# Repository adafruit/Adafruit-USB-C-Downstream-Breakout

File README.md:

## Adafruit USB C Breakout Board - Downstream Connection PCB

<a href="http://www.adafruit.com/products/4090"><br/>
Click here to purchase one from the Adafruit shop</a>

PCB files for the Adafruit USB C Breakout Board - Downstream Connection. Format is EagleCAD schematic and board layout
* https://www.adafruit.com/product/4090

### Description

Throw out all those Mini and Micro B USB cables you have in a plastic bin - the next generation of USB connectors is here with **USB C!** You will start to see these connectors pop up on all sorts of devices, as the industry moves from micro B or lightening to the new standard. Well, at least until the next standard comes out

USB C features a symmetric/reversible connector, more data pins and higher current output capability. But, for most developers, the pin usage you know and love from older USB will work just fine. This breakout gives you all the basics you need and a resistor configuration that mimics classic USB 2.0 for a downstream connection

The two 5.1K resistors on the **CC1** pins indicate to the upstream port to provide 5V and up to 1.5A (whether the upstream can supply that much current depends on what you're connecting to.

For most usages, you can just connect **VBUS** to your 5V input, **GND** to ground, and **D+** and **D-** as you expect. You can monitor the CC and SBU pins to determine cable polarity, or send side-band data. Or leave them disconnected

[For more details, we like this introduction to USB C app note](http://ww1.microchip.com/downloads/en/appnotes/00001953a.pdf)
### License

Adafruit invests time and resources providing this open source design, please support Adafruit and open-source hardware by purchasing products from [Adafruit](https://www.adafruit.com)!

Designed by Limor Fried/Ladyada for Adafruit Industries.

Creative Commons Attribution/Share-Alike, all text above must be included in any redistribution. See license.txt for additional details.

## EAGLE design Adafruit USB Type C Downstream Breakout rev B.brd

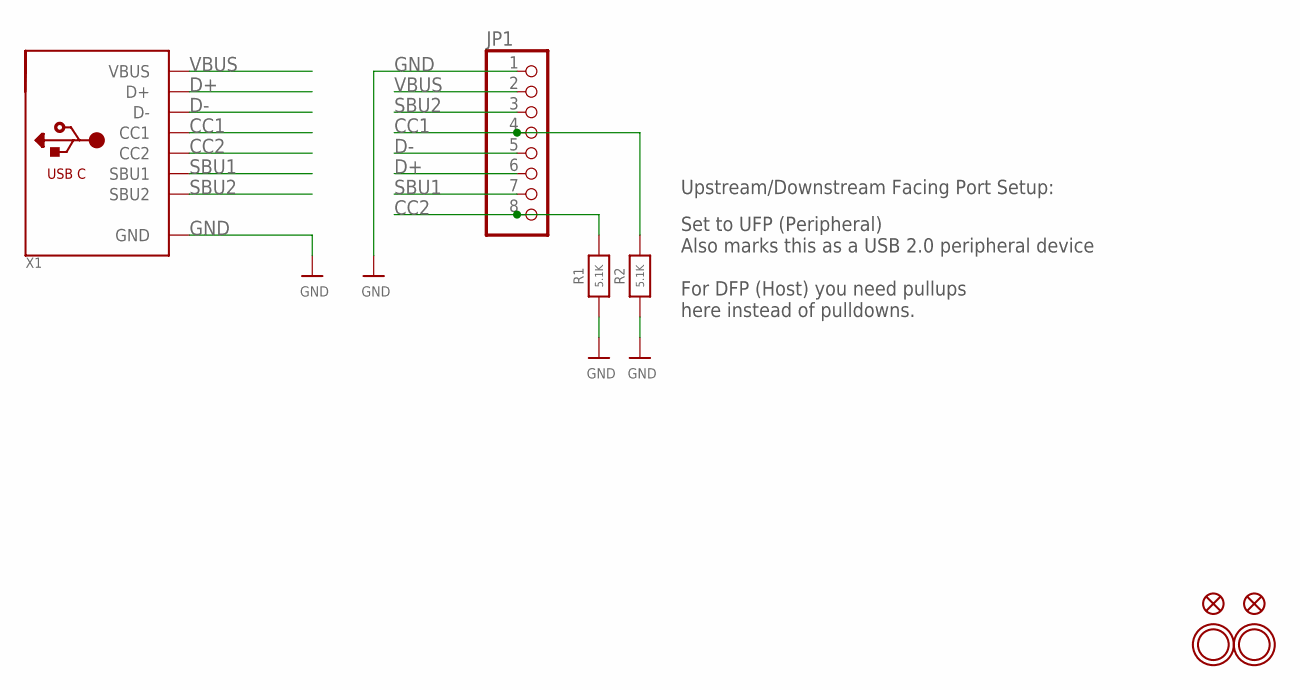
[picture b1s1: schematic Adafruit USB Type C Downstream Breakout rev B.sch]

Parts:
FID1, FID2: FIDUCIAL_1MM
JP1: HEADER-1X876MIL; 1X08_ROUND_76
R1, R2: 5.1K; 0603-NO
U$1, U$2: MOUNTINGHOLE2.5; MOUNTINGHOLE_2.5_PLATED
X1: USB_C; USB_C_CUSB31-CFM2AX-01-X

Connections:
CC1: JP1.4, R2.2, X1.A5 (CC1)
CC2: JP1.8, R1.2, X1.B5 (CC2)
D+: JP1.6, X1.A6 (D+), X1.B6 (D+)
D-: JP1.5, X1.A7 (D-), X1.B7 (D-)
GND: JP1.1, R1.1, R2.1, X1.A1B12 (GND), X1.B1A12 (GND)
SBU1: JP1.7, X1.A8 (SBU1)
SBU2: JP1.3, X1.B8 (SBU2)
VBUS: JP1.2, X1.A4B9 (VBUS), X1.B4A9 (VBUS)

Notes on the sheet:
Set to UFP (Peripheral) Also marks this as a USB 2.0 peripheral device For DFP (Host) you need pullups here instead of pulldowns.
Upstream/Downstream Facing Port Setup:

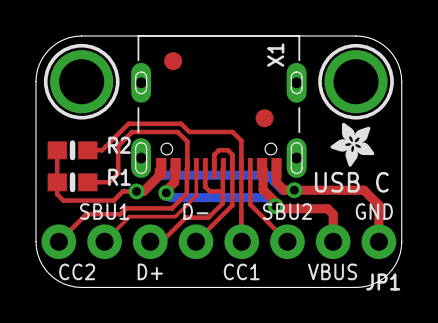
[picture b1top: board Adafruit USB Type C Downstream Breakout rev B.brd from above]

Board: 2 copper layers, 20.3 x 14.0 mm, 10 parts (1 on the bottom side), 8 nets.

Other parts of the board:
U$3: ADAFRUIT_2.5MM
U$8: PCBFEAT-REV-040

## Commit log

2019-02-06 Renamed files
2019-07-17 updated to use cookiecutter for pcb repos
2020-05-11 updating to rev b to fix issue #1

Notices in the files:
parts and their libraries:
microbuilder: This work is placed in the public domain, and may be freely used for commercial and non-commercial work with the following conditions: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
